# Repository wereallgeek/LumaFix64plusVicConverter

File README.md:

# LumaFix64 plus 85xx to 65xx VIC-II VDD selection
The LumaFix64 is not my design. 
This work is based on the brilliant work of Sven Peterson https://github.com/svenpetersen1965/LumaFix64
His version is based on <a href="https://www.lemon64.com/forum/viewtopic.php?t=40570&start=375">e5frog's LumaFix64 design</a>, which was released in March 7th, 2018 in the Lemon64.com forum. The changes in my design are:

* Added a VIC-II conversion to enable either shortboard or longboard voltages to the VIC-II, in order to be able to install 85xx VICs to an earlier (longboard) motherboard
* Added jumper to permit bypassing the C64 motherboard and push wires directly to the RF modulator unit (for aftermarker models that accepts it) in order to further reduce induced noise on the video lines

-- this design has not yet been tested

Sven advise that the Chroma potentiometer is not required but most LUMAFIX still includes it. If desired, it can be omitted, but this revision does not prepare solder points to do so, please use the potentiometer connections directly for that purpose. 

The LumaFix64 requires the precision round pin strips, because those are narrow enough not to break the socket of VIC-II chip. Since these pin strips are fragile, the LumaFix64 has to be handle with care.

Permission was initially received from e5frog for publishing these files, which was done in open hardware - the current development further enhance the design in pure open hardware ideology.

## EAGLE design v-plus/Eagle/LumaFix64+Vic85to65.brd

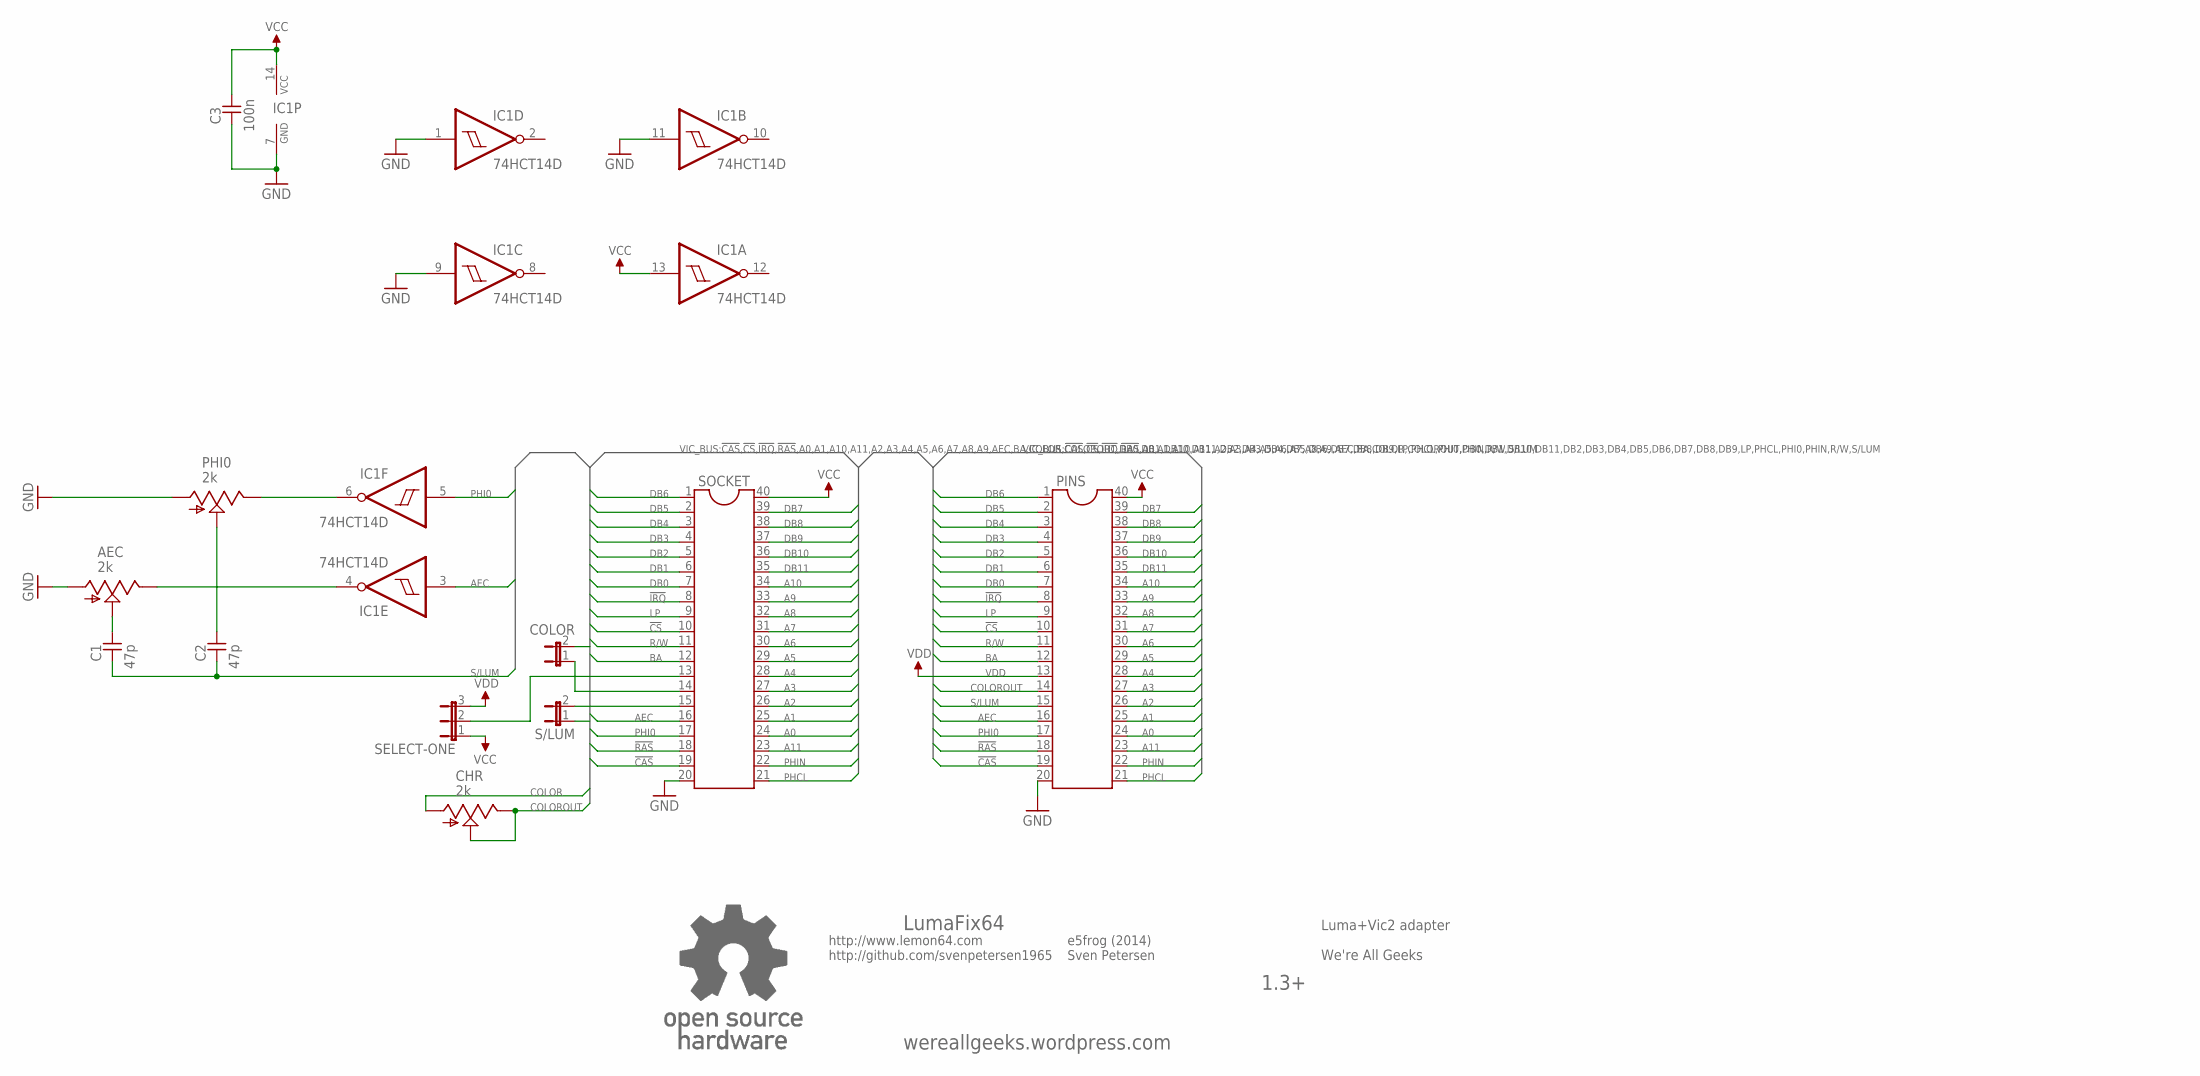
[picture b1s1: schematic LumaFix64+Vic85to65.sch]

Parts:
AEC: 2k; RJ9W
C1, C2: 47p; 0805
C3: 100n; 0805
CHR: 2k; RJ9W
COLOR: JP1E; JP1
IC1: 74HCT14D; SO14
PHI0: 2k; RJ9W
PINS: IC-PACKAGE_DIL40_10120540; BLK_10120540_2X20
S/LUM: JP1E; JP1
SELECT-ONE: JP2E; JP2
SOCKET: IC-PACKAGE_DIL40GS40P; GS40P
U$13: OPEN_SOURCE_HW; OPENHW

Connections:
!CAS: PINS.19, SOCKET.19
!CS: PINS.10, SOCKET.10
!IRQ: PINS.8, SOCKET.8
!RAS: PINS.18, SOCKET.18
A0: PINS.24, SOCKET.24
A1: PINS.25, SOCKET.25
A2: PINS.26, SOCKET.26
A3: PINS.27, SOCKET.27
A4: PINS.28, SOCKET.28
A5: PINS.29, SOCKET.29
A6: PINS.30, SOCKET.30
A7: PINS.31, SOCKET.31
A8: PINS.32, SOCKET.32
A9: PINS.33, SOCKET.33
A10: PINS.34, SOCKET.34
A11: PINS.23, SOCKET.23
AEC: IC1.3 (I), PINS.16, SOCKET.16
BA: PINS.12, SOCKET.12
COLOR: CHR.A, COLOR.2
COLOROUT: CHR.E, CHR.S, PINS.14
DB0: PINS.7, SOCKET.7
DB1: PINS.6, SOCKET.6
DB2: PINS.5, SOCKET.5
DB3: PINS.4, SOCKET.4
DB4: PINS.3, SOCKET.3
DB5: PINS.2, SOCKET.2
DB6: PINS.1, SOCKET.1
DB7: PINS.39, SOCKET.39
DB8: PINS.38, SOCKET.38
DB9: PINS.37, SOCKET.37
DB10: PINS.36, SOCKET.36
DB11: PINS.35, SOCKET.35
GND: AEC.A, C3.1, IC1.1 (I), IC1.7 (GND), IC1.9 (I), IC1.11 (I), PHI0.A, PINS.20, SOCKET.20
LP: PINS.9, SOCKET.9
unnamed: SELECT-ONE.2, SOCKET.13
unnamed: COLOR.1, SOCKET.14
unnamed: S/LUM.2, SOCKET.15
unnamed: AEC.S, C1.2
unnamed: C2.2, PHI0.S
unnamed: AEC.E, IC1.4 (O)
unnamed: IC1.6 (O), PHI0.E
PHCL: PINS.21, SOCKET.21
PHI0: IC1.5 (I), PINS.17, SOCKET.17
PHIN: PINS.22, SOCKET.22
R/W: PINS.11, SOCKET.11
S/LUM: C1.1, C2.1, PINS.15, S/LUM.1
VCC: C3.2, IC1.13 (I), IC1.14 (VCC), PINS.40, SELECT-ONE.1, SOCKET.40
VDD: PINS.13, SELECT-ONE.3

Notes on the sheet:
LumaFix64
http://www.lemon64.com http://github.com/svenpetersen1965
e5frog (2014) Sven Petersen
1.3+
Luma+Vic2 adapter
We're All Geeks
wereallgeeks.wordpress.com

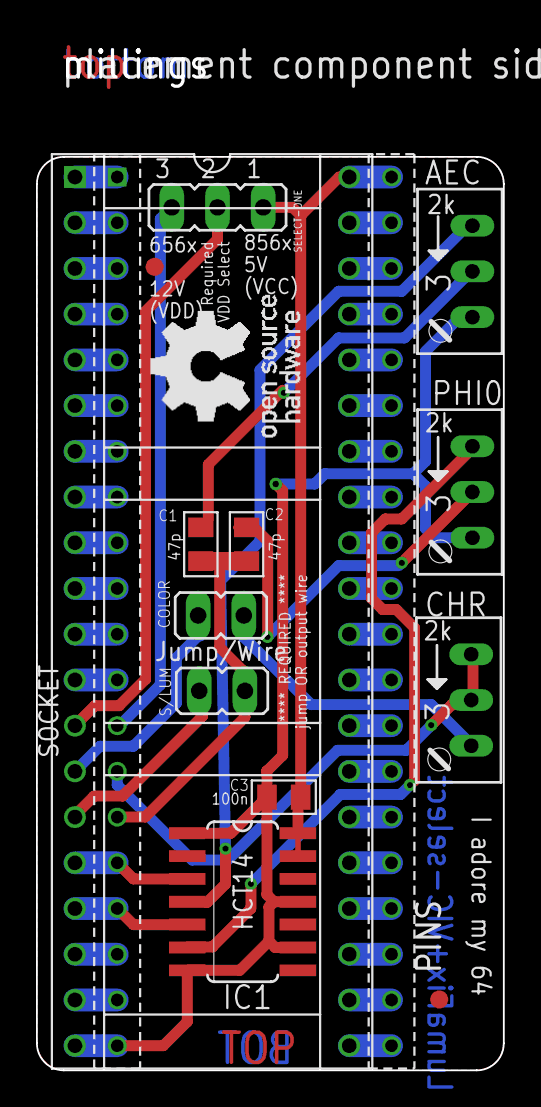
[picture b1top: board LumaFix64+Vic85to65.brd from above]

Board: 2 copper layers, 25.9 x 57.4 mm, 17 parts (0 on the bottom side), 48 nets.

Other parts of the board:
U$7: 2LAYER
U$9: PCB-TITLE/
U$10, U$11: SMD_REF_R1MM

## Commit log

2023-08-26 Initial revision. Addition - VIC-II conversion from 85xx to 65xx motherboard Addition - output jumpers Change - removal of CHR options. Can be implemented directly on pot pins Change - changed potent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
2023-08-26 removal of initial v1.2 - still available at the source branch.
2023-08-26 updated Readme file
2023-08-26 documentation update
